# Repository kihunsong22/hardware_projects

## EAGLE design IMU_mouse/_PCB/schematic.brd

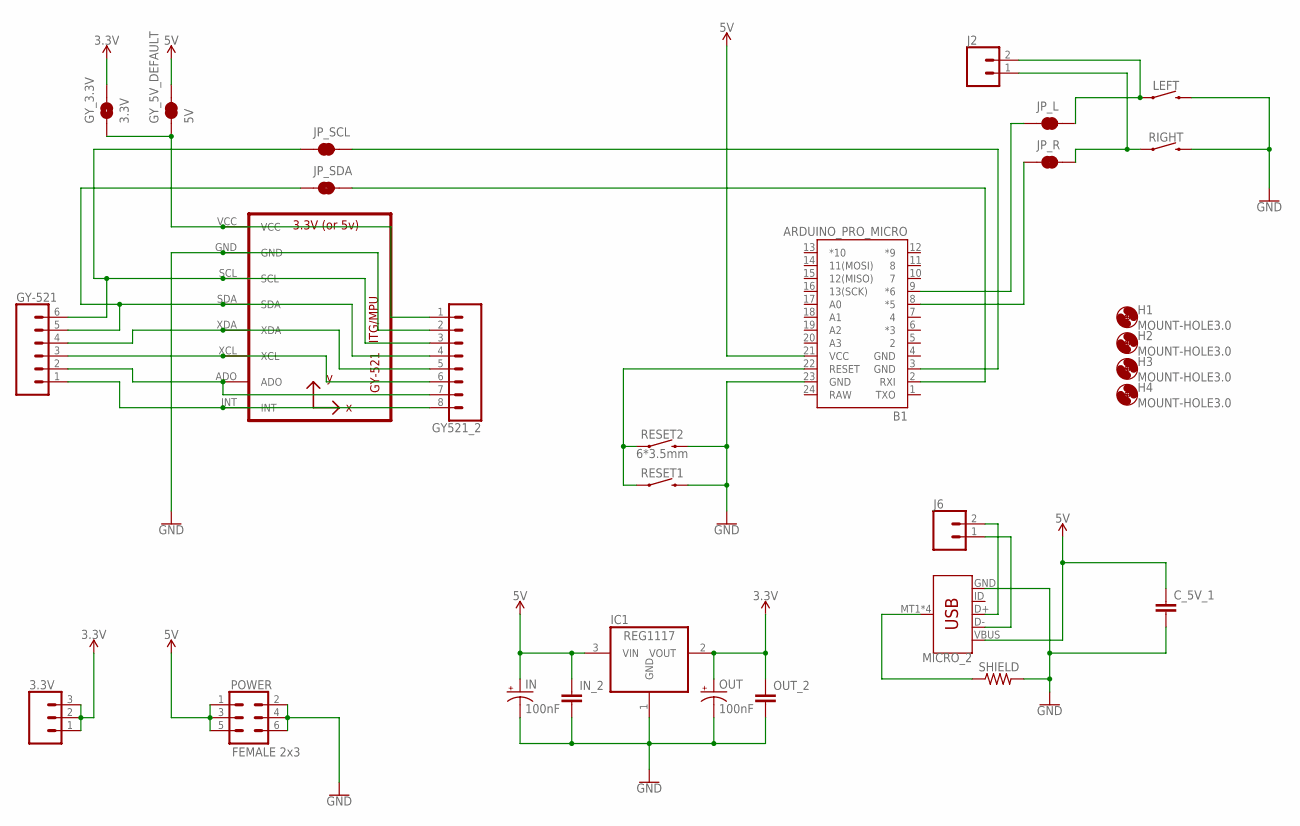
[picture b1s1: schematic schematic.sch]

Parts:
3.3V: CONN_03; 1X03
B1: ARDUINO_PRO_MICRO; SPARKFUN_PRO_MICRO
C_5V_1: C-EUC0805; C0805
GY521_2: CONN_08"; 1X08
GY-521: CONN_06LOCK; 1X06_LOCK
GY_3.3V: 3.3V; SMT-JUMPER_2_NO_NO-SILK
GY_5V_DEFAULT: 5V; SMT-JUMPER_2_NC_TRACE_SILK
H1, H2, H3, H4: MOUNT-HOLE3.0; 3,0
IC1: REG1117; SOT223
IN: 100nF; E2,5-5
IN_2: C-EUC0805; C0805
J2, J6: CONN_02LOCK; 1X02_LOCK
JP_L: JUMPER-SMT_2_NC_TRACE_SILK; SMT-JUMPER_2_NC_TRACE_SILK
JP_R: JUMPER-SMT_2_NC_TRACE_SILK; SMT-JUMPER_2_NC_TRACE_SILK
JP_SCL: JUMPER-SMT_2_NC_TRACE_SILK; SMT-JUMPER_2_NC_TRACE_SILK
JP_SDA: JUMPER-SMT_2_NC_TRACE_SILK; SMT-JUMPER_2_NC_TRACE_SILK
LEFT: MOMENTARY-SWITCH-SPST-PTH-6.0MM; TACTILE_SWITCH_PTH_6.0MM
MICRO_2: USB_MICRO-B_SMT; USB-MICROB
OUT: 100nF; E2,5-5
OUT_2: C-EUC0805; C0805
POWER: FEMALE 2x3; 2X3
RESET1: MOMENTARY-SWITCH-SPST-PTH-6.0MM; TACTILE_SWITCH_PTH_6.0MM
RESET2: 6*3.5mm; TACTILE_SWITCH_SMD_6.0X3.5MM
RIGHT: MOMENTARY-SWITCH-SPST-PTH-6.0MM; TACTILE_SWITCH_PTH_6.0MM
SHIELD: R-US_R0805; R0805
U1: GY-521MPU6050; GY-521

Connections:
3.3V: 3.3V.1, 3.3V.2, 3.3V.3, GY_3.3V.2, IC1.2 (VOUT), OUT.+, OUT_2.1
5V: B1.21 (VCC), C_5V_1.1, GY_5V_DEFAULT.2, IC1.3 (VIN), IN.+, IN_2.1, MICRO_2.VBUS, POWER.1, POWER.3, POWER.5
D+: J6.2, MICRO_2.D+
D-: J6.1, MICRO_2.D-
GND: B1.4 (GND), B1.23 (GND), C_5V_1.2, GY521_2.2, IC1.1 (GND), IN.-, IN_2.2, LEFT.3 (2), MICRO_2.GND, OUT.-, OUT_2.2, POWER.2, POWER.4, POWER.6, RESET1.3 (2), RESET2.2, RIGHT.3 (2), SHIELD.2, U1.GND
unnamed: J2.2, JP_L.2, LEFT.1
unnamed: J2.1, JP_R.2, RIGHT.1
unnamed: B1.8 (*5), JP_R.1
unnamed: B1.9 (*6), JP_L.1
unnamed: GY521_2.1, GY_3.3V.1, GY_5V_DEFAULT.1, U1.VCC
unnamed: B1.22 (RESET), RESET1.1, RESET2.1
unnamed: MICRO_2.MT1 (SHIELD), MICRO_2.MT2 (SHIELD), MICRO_2.P$1 (SHIELD), MICRO_2.P$2 (SHIELD), SHIELD.1
unnamed: B1.2 (RXI), JP_SDA.2
unnamed: B1.3 (GND), JP_SCL.2
unnamed: GY521_2.8, GY-521.1, U1.INT
unnamed: GY521_2.7, GY-521.2, U1.ADO
unnamed: GY521_2.6, GY-521.3, U1.XCL
unnamed: GY521_2.5, GY-521.4, U1.XDA
RAW: B1.24 (RAW)
SCL: GY521_2.3, GY-521.6, JP_SCL.1, U1.SCL
SDA: GY521_2.4, GY-521.5, JP_SDA.1, U1.SDA

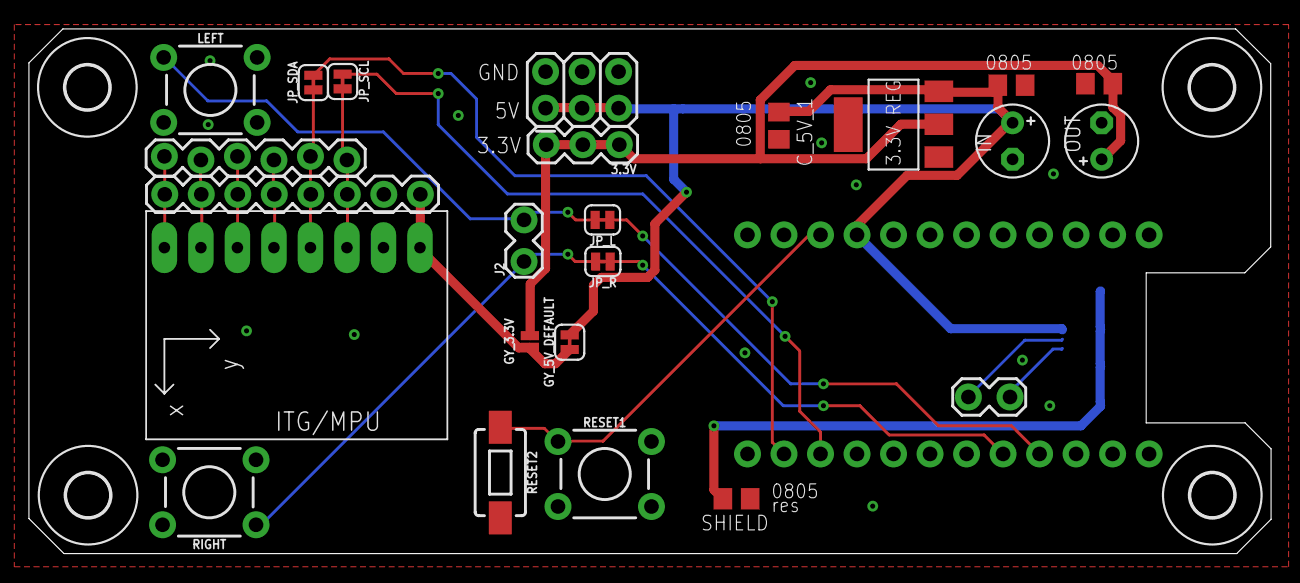
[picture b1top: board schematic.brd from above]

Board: 2 copper layers, 86.4 x 36.5 mm, 30 parts (1 on the bottom side), 20 nets.

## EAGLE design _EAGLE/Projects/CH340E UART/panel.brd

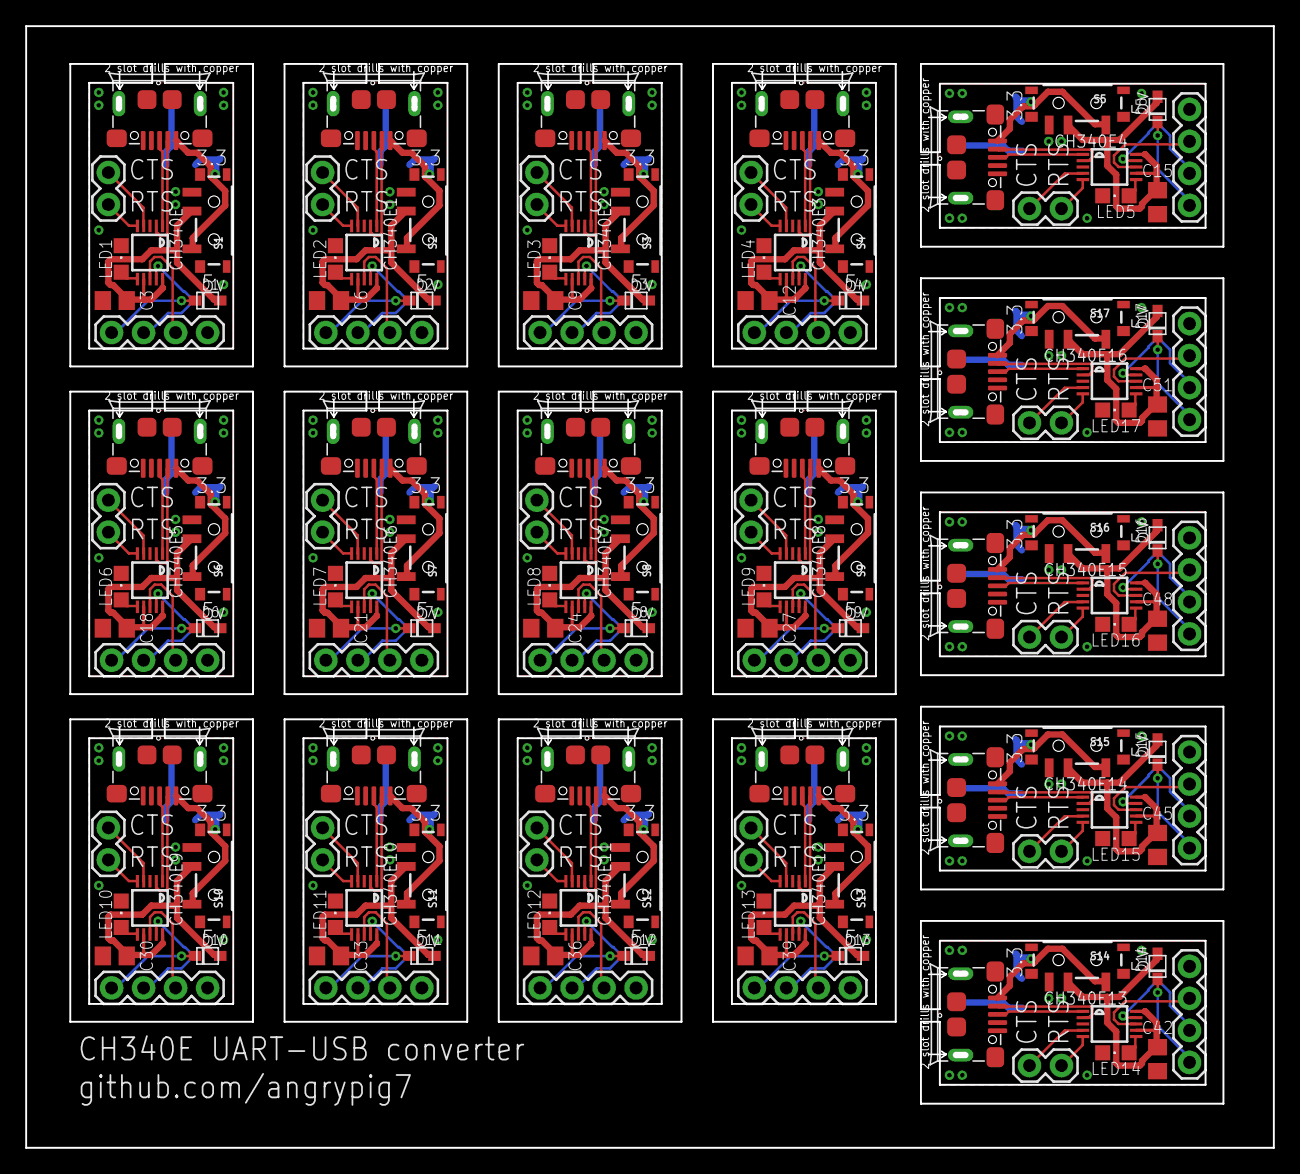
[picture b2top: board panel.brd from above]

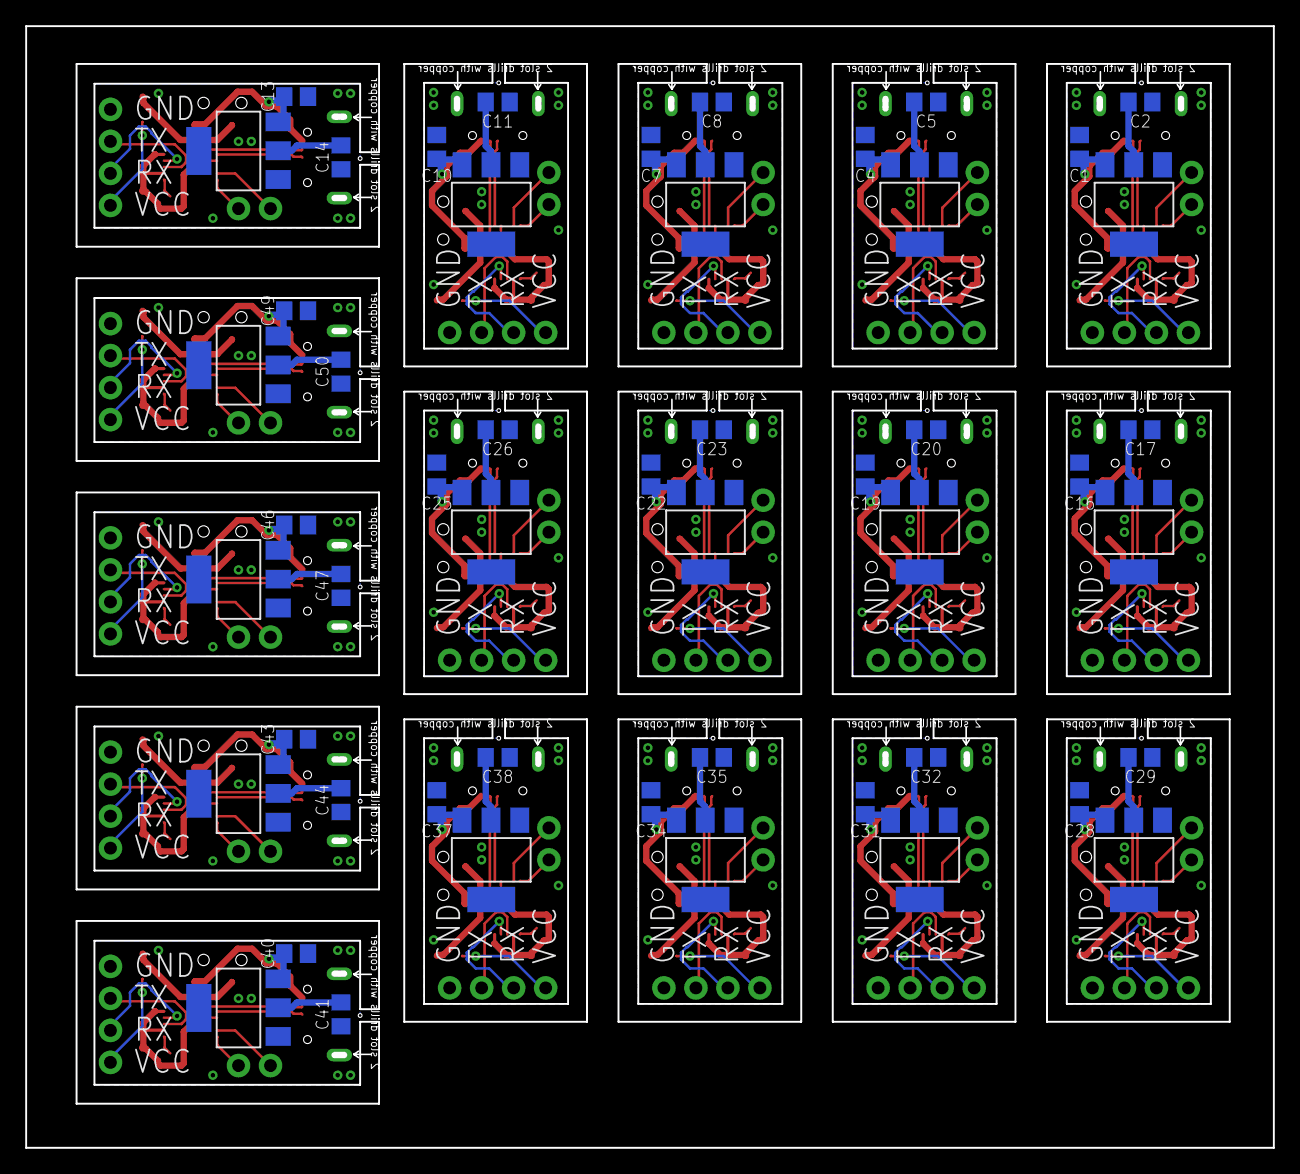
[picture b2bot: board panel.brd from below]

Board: 2 copper layers, 99.0 x 89.0 mm, 187 parts (51 on the bottom side), 204 nets.

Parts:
C1, C2, C3, C4, C5, C6, C7, C8, C9, C10, C11, C12, C13, C14, C15, C16, C17, C18, C19, C20, C21, C22, C23, C24, C25, C26, C27, C28, C29, C30, C31, C32, C33, C34, C35, C36, C37, C38, C39, C40, C41, C42, C43, C44, C45, C46, C47, C48, C49, C50, C51: 100nF; C0805
CH340E, CH340E1, CH340E2, CH340E3, CH340E4, CH340E5, CH340E6, CH340E7, CH340E8, CH340E9, CH340E10, CH340E11, CH340E12, CH340E13, CH340E14, CH340E15, CH340E16: CH340ESMD; MSOP10
D1, D2, D3, D4, D5, D6, D7, D8, D9, D10, D11, D12, D13, D14, D15, D16, D17: SOD-323F
IC1, IC2, IC3, IC4, IC5, IC6, IC7, IC8, IC9, IC10, IC11, IC12, IC13, IC14, IC15, IC16, IC17: REG1117; SOT223
J1, J3, J5, J7, J9, J11, J13, J15, J17, J19, J21, J23, J25, J27, J29, J31, J33: 1X04
J2, J4, J6, J8, J10, J12, J14, J16, J18, J20, J22, J24, J26, J28, J30, J32, J34: 1X02
LED1, LED2, LED3, LED4, LED5, LED6, LED7, LED8, LED9, LED10, LED11, LED12, LED13, LED14, LED15, LED16, LED17: CHIPLED_0805
S1, S2, S3, S4, S5, S6, S7, S8, S9, S10, S11, S12, S13, S14, S15, S16, S17: SWITCH_SPST_SMD_A
USB1, USB2, USB3, USB4, USB5, USB6, USB7, USB8, USB9, USB10, USB11, USB12, USB13, USB14, USB15, USB16, USB17: ST-USB-001G; MICRO-USB5+4P-SMD-0.65-B

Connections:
3V1: C5.1, IC2.2
3V2: C8.1, IC3.2
3V3: C2.1, IC1.2
3V4: C11.1, IC4.2
3V5: C14.1, IC5.2
3V6: C17.1, IC6.2
3V7: C20.1, IC7.2
3V8: C23.1, IC8.2
3V9: C26.1, IC9.2
3V10: C29.1, IC10.2
3V11: C32.1, IC11.2
3V12: C35.1, IC12.2
3V13: C38.1, IC13.2
3V14: C41.1, IC14.2
3V15: C44.1, IC15.2
3V16: C47.1, IC16.2
3V17: C50.1, IC17.2
5V: C1.1, IC1.3, S1.3, USB2.1
5V1: C4.1, IC2.3, S2.3, USB1.1
5V2: C7.1, IC3.3, S3.3, USB3.1
5V3: C10.1, IC4.3, S4.3, USB4.1
5V4: C13.1, IC5.3, S5.3, USB5.1
5V5: C16.1, IC6.3, S6.3, USB6.1
5V6: C19.1, IC7.3, S7.3, USB7.1
5V7: C22.1, IC8.3, S8.3, USB8.1
5V8: C25.1, IC9.3, S9.3, USB9.1
5V9: C28.1, IC10.3, S10.3, USB10.1
5V10: C31.1, IC11.3, S11.3, USB11.1
5V11: C34.1, IC12.3, S12.3, USB12.1
5V12: C37.1, IC13.3, S13.3, USB13.1
5V13: C40.1, IC14.3, S14.3, USB14.1
5V14: C43.1, IC15.3, S15.3, USB15.1
5V15: C46.1, IC16.3, S16.3, USB16.1
5V16: C49.1, IC17.3, S17.3, USB17.1
CTS: CH340E.5, J2.1
CTS1: CH340E1.5, J4.1
CTS2: CH340E2.5, J6.1
CTS3: CH340E3.5, J8.1
CTS4: CH340E4.5, J10.1
CTS5: CH340E5.5, J12.1
CTS6: CH340E6.5, J14.1
CTS7: CH340E7.5, J16.1
CTS8: CH340E8.5, J18.1
CTS9: CH340E9.5, J20.1
CTS10: CH340E10.5, J22.1
CTS11: CH340E11.5, J24.1
CTS12: CH340E12.5, J26.1
CTS13: CH340E13.5, J28.1
CTS14: CH340E14.5, J30.1
CTS15: CH340E15.5, J32.1
CTS16: CH340E16.5, J34.1
GND: C1.2, C2.2, C3.2, CH340E.3, IC1.1, J1.4, LED1.C, USB2.5, USB2.S1, USB2.S2, USB2.S3, USB2.S4, USB2.S5, USB2.S6
GND1: C4.2, C5.2, C6.2, CH340E1.3, IC2.1, J3.4, LED2.C, USB1.5, USB1.S1, USB1.S2, USB1.S3, USB1.S4, USB1.S5, USB1.S6
GND2: C7.2, C8.2, C9.2, CH340E2.3, IC3.1, J5.4, LED3.C, USB3.5, USB3.S1, USB3.S2, USB3.S3, USB3.S4, USB3.S5, USB3.S6
GND3: C10.2, C11.2, C12.2, CH340E3.3, IC4.1, J7.4, LED4.C, USB4.5, USB4.S1, USB4.S2, USB4.S3, USB4.S4, USB4.S5, USB4.S6
GND4: C13.2, C14.2, C15.2, CH340E4.3, IC5.1, J9.4, LED5.C, USB5.5, USB5.S1, USB5.S2, USB5.S3, USB5.S4, USB5.S5, USB5.S6
GND5: C16.2, C17.2, C18.2, CH340E5.3, IC6.1, J11.4, LED6.C, USB6.5, USB6.S1, USB6.S2, USB6.S3, USB6.S4, USB6.S5, USB6.S6
GND6: C19.2, C20.2, C21.2, CH340E6.3, IC7.1, J13.4, LED7.C, USB7.5, USB7.S1, USB7.S2, USB7.S3, USB7.S4, USB7.S5, USB7.S6
GND7: C22.2, C23.2, C24.2, CH340E7.3, IC8.1, J15.4, LED8.C, USB8.5, USB8.S1, USB8.S2, USB8.S3, USB8.S4, USB8.S5, USB8.S6
GND8: C25.2, C26.2, C27.2, CH340E8.3, IC9.1, J17.4, LED9.C, USB9.5, USB9.S1, USB9.S2, USB9.S3, USB9.S4, USB9.S5, USB9.S6
GND9: C28.2, C29.2, C30.2, CH340E9.3, IC10.1, J19.4, LED10.C, USB10.5, USB10.S1, USB10.S2, USB10.S3, USB10.S4, USB10.S5, USB10.S6
GND10: C31.2, C32.2, C33.2, CH340E10.3, IC11.1, J21.4, LED11.C, USB11.5, USB11.S1, USB11.S2, USB11.S3, USB11.S4, USB11.S5, USB11.S6
GND11: C34.2, C35.2, C36.2, CH340E11.3, IC12.1, J23.4, LED12.C, USB12.5, USB12.S1, USB12.S2, USB12.S3, USB12.S4, USB12.S5, USB12.S6
GND12: C37.2, C38.2, C39.2, CH340E12.3, IC13.1, J25.4, LED13.C, USB13.5, USB13.S1, USB13.S2, USB13.S3, USB13.S4, USB13.S5, USB13.S6
GND13: C40.2, C41.2, C42.2, CH340E13.3, IC14.1, J27.4, LED14.C, USB14.5, USB14.S1, USB14.S2, USB14.S3, USB14.S4, USB14.S5, USB14.S6
GND14: C43.2, C44.2, C45.2, CH340E14.3, IC15.1, J29.4, LED15.C, USB15.5, USB15.S1, USB15.S2, USB15.S3, USB15.S4, USB15.S5, USB15.S6
GND15: C46.2, C47.2, C48.2, CH340E15.3, IC16.1, J31.4, LED16.C, USB16.5, USB16.S1, USB16.S2, USB16.S3, USB16.S4, USB16.S5, USB16.S6
GND16: C49.2, C50.2, C51.2, CH340E16.3, IC17.1, J33.4, LED17.C, USB17.5, USB17.S1, USB17.S2, USB17.S3, USB17.S4, USB17.S5, USB17.S6
unnamed: CH340E.6, LED1.A
unnamed: CH340E1.6, LED2.A
unnamed: CH340E2.6, LED3.A
unnamed: CH340E3.6, LED4.A
unnamed: CH340E4.6, LED5.A
unnamed: CH340E5.6, LED6.A
unnamed: CH340E6.6, LED7.A
unnamed: CH340E7.6, LED8.A
unnamed: CH340E8.6, LED9.A
unnamed: CH340E9.6, LED10.A
unnamed: CH340E10.6, LED11.A
unnamed: CH340E11.6, LED12.A
unnamed: CH340E12.6, LED13.A
unnamed: CH340E13.6, LED14.A
unnamed: CH340E14.6, LED15.A
unnamed: CH340E15.6, LED16.A
unnamed: CH340E16.6, LED17.A
RTS: CH340E.4, J2.2
RTS1: CH340E1.4, J4.2
RTS2: CH340E2.4, J6.2
RTS3: CH340E3.4, J8.2
RTS4: CH340E4.4, J10.2
RTS5: CH340E5.4, J12.2
RTS6: CH340E6.4, J14.2
RTS7: CH340E7.4, J16.2
RTS8: CH340E8.4, J18.2
RTS9: CH340E9.4, J20.2
RTS10: CH340E10.4, J22.2
RTS11: CH340E11.4, J24.2
RTS12: CH340E12.4, J26.2
RTS13: CH340E13.4, J28.2
RTS14: CH340E14.4, J30.2
RTS15: CH340E15.4, J32.2
RTS16: CH340E16.4, J34.2
RX: CH340E.9, J1.2
RX1: CH340E1.9, J3.2
RX2: CH340E2.9, J5.2
RX3: CH340E3.9, J7.2
RX4: CH340E4.9, J9.2
RX5: CH340E5.9, J11.2
RX6: CH340E6.9, J13.2
RX7: CH340E7.9, J15.2
RX8: CH340E8.9, J17.2
RX9: CH340E9.9, J19.2
RX10: CH340E10.9, J21.2
RX11: CH340E11.9, J23.2
RX12: CH340E12.9, J25.2
RX13: CH340E13.9, J27.2
RX14: CH340E14.9, J29.2
RX15: CH340E15.9, J31.2
RX16: CH340E16.9, J33.2
TX: CH340E.8, J1.3
TX1: CH340E1.8, J3.3
TX2: CH340E2.8, J5.3
TX3: CH340E3.8, J7.3
TX4: CH340E4.8, J9.3
TX5: CH340E5.8, J11.3
TX6: CH340E6.8, J13.3
TX7: CH340E7.8, J15.3
TX8: CH340E8.8, J17.3
TX9: CH340E9.8, J19.3
TX10: CH340E10.8, J21.3
TX11: CH340E11.8, J23.3
TX12: CH340E12.8, J25.3
TX13: CH340E13.8, J27.3
TX14: CH340E14.8, J29.3
TX15: CH340E15.8, J31.3
TX16: CH340E16.8, J33.3
USBN: CH340E.2, USB2.2
USBN1: CH340E1.2, USB1.2
USBN2: CH340E2.2, USB3.2
USBN3: CH340E3.2, USB4.2
USBN4: CH340E4.2, USB5.2
USBN5: CH340E5.2, USB6.2
USBN6: CH340E6.2, USB7.2
USBN7: CH340E7.2, USB8.2
USBN8: CH340E8.2, USB9.2
USBN9: CH340E9.2, USB10.2
USBN10: CH340E10.2, USB11.2
USBN11: CH340E11.2, USB12.2
USBN12: CH340E12.2, USB13.2
USBN13: CH340E13.2, USB14.2
USBN14: CH340E14.2, USB15.2
USBN15: CH340E15.2, USB16.2
USBN16: CH340E16.2, USB17.2
USBP: CH340E.1, USB2.3
USBP1: CH340E1.1, USB1.3
USBP2: CH340E2.1, USB3.3
USBP3: CH340E3.1, USB4.3
USBP4: CH340E4.1, USB5.3
USBP5: CH340E5.1, USB6.3
USBP6: CH340E6.1, USB7.3
USBP7: CH340E7.1, USB8.3
USBP8: CH340E8.1, USB9.3
USBP9: CH340E9.1, USB10.3
USBP10: CH340E10.1, USB11.3
USBP11: CH340E11.1, USB12.3
USBP12: CH340E12.1, USB13.3
USBP13: CH340E13.1, USB14.3
USBP14: CH340E14.1, USB15.3
USBP15: CH340E15.1, USB16.3
USBP16: CH340E16.1, USB17.3
VCC: C3.1, CH340E.7, CH340E.10, D1.A, S1.2
VCC1: C6.1, CH340E1.7, CH340E1.10, D2.A, S2.2
VCC2: C9.1, CH340E2.7, CH340E2.10, D3.A, S3.2
VCC3: C12.1, CH340E3.7, CH340E3.10, D4.A, S4.2
VCC4: C15.1, CH340E4.7, CH340E4.10, D5.A, S5.2
VCC5: C18.1, CH340E5.7, CH340E5.10, D6.A, S6.2
VCC6: C21.1, CH340E6.7, CH340E6.10, D7.A, S7.2
VCC7: C24.1, CH340E7.7, CH340E7.10, D8.A, S8.2
VCC8: C27.1, CH340E8.7, CH340E8.10, D9.A, S9.2
VCC9: C30.1, CH340E9.7, CH340E9.10, D10.A, S10.2
VCC10: C33.1, CH340E10.7, CH340E10.10, D11.A, S11.2
VCC11: C36.1, CH340E11.7, CH340E11.10, D12.A, S12.2
VCC12: C39.1, CH340E12.7, CH340E12.10, D13.A, S13.2
VCC13: C42.1, CH340E13.7, CH340E13.10, D14.A, S14.2
VCC14: C45.1, CH340E14.7, CH340E14.10, D15.A, S15.2
VCC15: C48.1, CH340E15.7, CH340E15.10, D16.A, S16.2
VCC16: C51.1, CH340E16.7, CH340E16.10, D17.A, S17.2
VCC_D: D1.C, J1.1
VCC_D1: D2.C, J3.1
VCC_D2: D3.C, J5.1
VCC_D3: D4.C, J7.1
VCC_D4: D5.C, J9.1
VCC_D5: D6.C, J11.1
VCC_D6: D7.C, J13.1
VCC_D7: D8.C, J15.1
VCC_D8: D9.C, J17.1
VCC_D9: D10.C, J19.1
VCC_D10: D11.C, J21.1
VCC_D11: D12.C, J23.1
VCC_D12: D13.C, J25.1
VCC_D13: D14.C, J27.1
VCC_D14: D15.C, J29.1
VCC_D15: D16.C, J31.1
VCC_D16: D17.C, J33.1

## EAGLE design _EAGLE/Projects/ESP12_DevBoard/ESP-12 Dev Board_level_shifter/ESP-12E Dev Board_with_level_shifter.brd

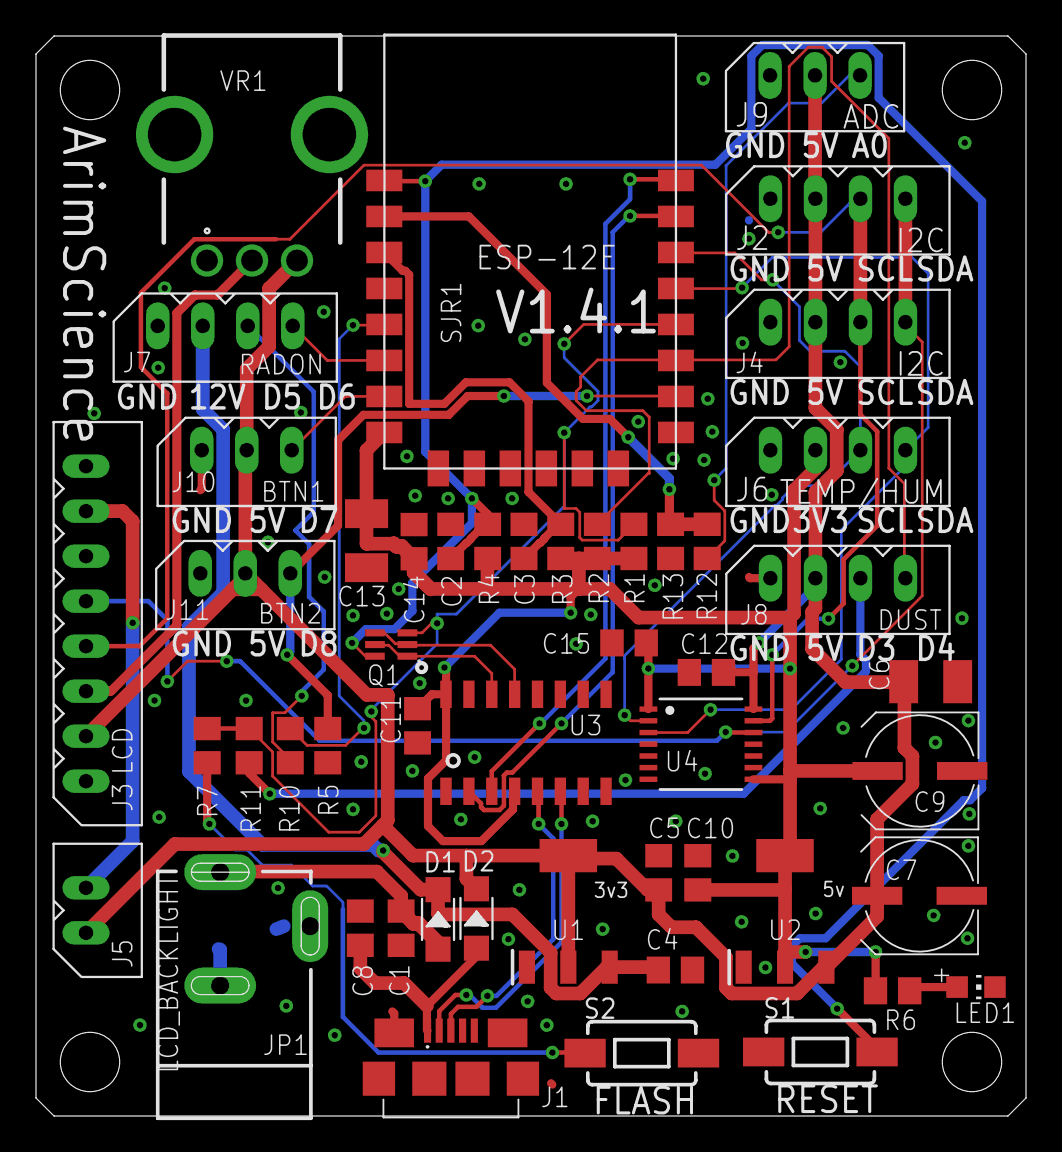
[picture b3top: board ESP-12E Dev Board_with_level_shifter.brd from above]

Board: 2 copper layers, 55.0 x 60.0 mm, 50 parts (0 on the bottom side), 32 nets.

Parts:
C1, C4: 10uF; C0805
C2, C3, C8, C11, C12, C14, C15: 100nF; C0805
C5, C10: 22uF; C0805
C6, C13: 100uF; SMC_B
C7, C9: 220uF; UD-6,3X7,7_NICHICON
D1, D2: 1N5819W; SOD-123
J1: ZX62-B-5PA(33); ZX62B5PA33
J2, J4: I2C; 5267-4
J3: LCD; 5267-8
J5: LCD_BACKLIGHT; 5267-2
J6: TEMP/HUM; 5267-4
J7: RADON; 5267-4
J8: DUST; 5267-4
J9: ADC; 5267-3
J10: BTN1; 5267-3
J11: BTN2; 5267-3
JP1: POWER_JACKSLT; POWER_JACK_SLOT
LED1: green; CHIP-LED0805
Q1: UMH3N; SOT65P210X100-6N
R1, R2, R3, R4, R5, R6: 10k; R0805
R7, R10, R11: 470Ω; R0805
R12: 47k(1%); R0805
R13: 10k(1%); R0805
S1: RST; TACTILE_SWITCH_SMD_6.0X3.5MM
S2: FLASH; TACTILE_SWITCH_SMD_6.0X3.5MM
SJR1: ESP-12E; ESP8266-ESP12E
U1: 5V_REG; SOT230P700X170-4N
U2: 3V3_REG; SOT230P700X170-4N
U3: CH340C; SOIC16
U4: TXS0104; TSSOP14
VR1: RK09K1130AAU; RK09K1130BGM

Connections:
3.3V: C9.+, C10.2, C11.2, C13.+, C14.2, C15.2, J6.P$2, R1.1, R2.1, R3.1, R4.1, R6.1, SJR1.8, U2.2, U2.4, U3.4, U3.16, U4.1, U4.8
5V: C5.1, C6.+, C7.+, C12.2, D2.-, J2.P$2, J3.P$2, J4.P$2, J5.P$1, J8.P$2, J9.P$2, J10.P$2, J11.P$2, U1.2, U1.4, U2.3, U4.14, VR1.3
12V: C4.1, D1.-, J7.P$2, U1.3
ADC: R12.1, R13.2, SJR1.2
D+_USB: J1.D+, U3.5
D-_USB: J1.D-, U3.6
DTR: Q1.2, Q1.4, U3.13
EN: C3.2, R3.2, SJR1.3
GND: C1.1, C2.1, C3.1, C4.2, C5.2, C6.-, C7.-, C8.1, C9.-, C10.1, C11.1, C12.1, C13.-, C14.1, C15.1, J1.GND, J1.SHIELD_1, J1.SHIELD_2, J1.SHIELD_3, J1.SHIELD_4, J1.SHIELD_5, J1.SHIELD_6, J2.P$1, J3.P$1, J3.P$8, J4.P$1, J6.P$1, J7.P$1, J8.P$1, J9.P$1, J10.P$1, J11.P$1, JP1.GND@1, JP1.GND@2, LED1.C, R5.1, R13.1, S1.2, S2.2, SJR1.9, U1.1, U2.1, U3.1, U4.7, VR1.1
GPIO0: Q1.3, R1.2, R7.1, R11.1, SJR1.12
GPIO2: J8.P$4, R2.2, SJR1.11
GPIO4: J6.P$4, SJR1.13, U4.3
GPIO5: J6.P$3, SJR1.14, U4.2
GPIO12: J7.P$4, SJR1.6
GPIO13: J10.P$3, SJR1.7
GPIO14: R10.1, SJR1.5
GPIO15: J11.P$3, R5.2, SJR1.10
LED+: J3.P$7, J5.P$2
unnamed: J3.P$3, VR1.2
unnamed: C1.2, D1.+, JP1.PWR
unnamed: LED1.A, R6.2
unnamed: J9.P$3, R12.2
unnamed: J7.P$3, R10.2
unnamed: J8.P$3, R11.2
unnamed: C8.2, D2.+, J1.VCC
POWER1: R7.2, S2.1
RST: C2.2, Q1.6, R4.2, S1.1, SJR1.1
RTS: Q1.1, Q1.5, U3.14
RXD: SJR1.15, U3.2
SCL_5V: J2.P$3, J3.P$4, J4.P$3, U4.13
SDA_5V: J2.P$4, J3.P$5, J4.P$4, U4.12
TXD: SJR1.16, U3.3

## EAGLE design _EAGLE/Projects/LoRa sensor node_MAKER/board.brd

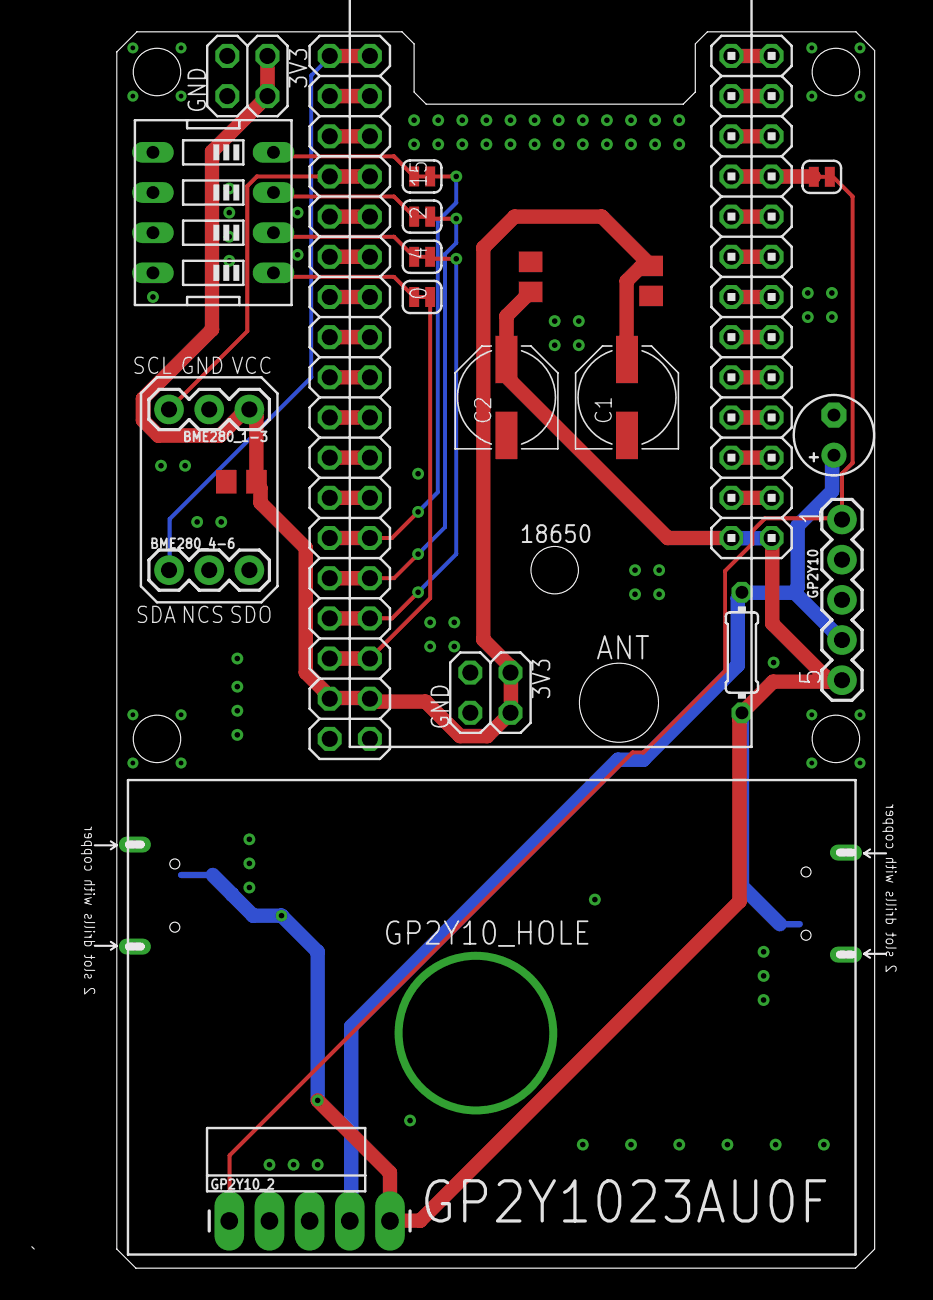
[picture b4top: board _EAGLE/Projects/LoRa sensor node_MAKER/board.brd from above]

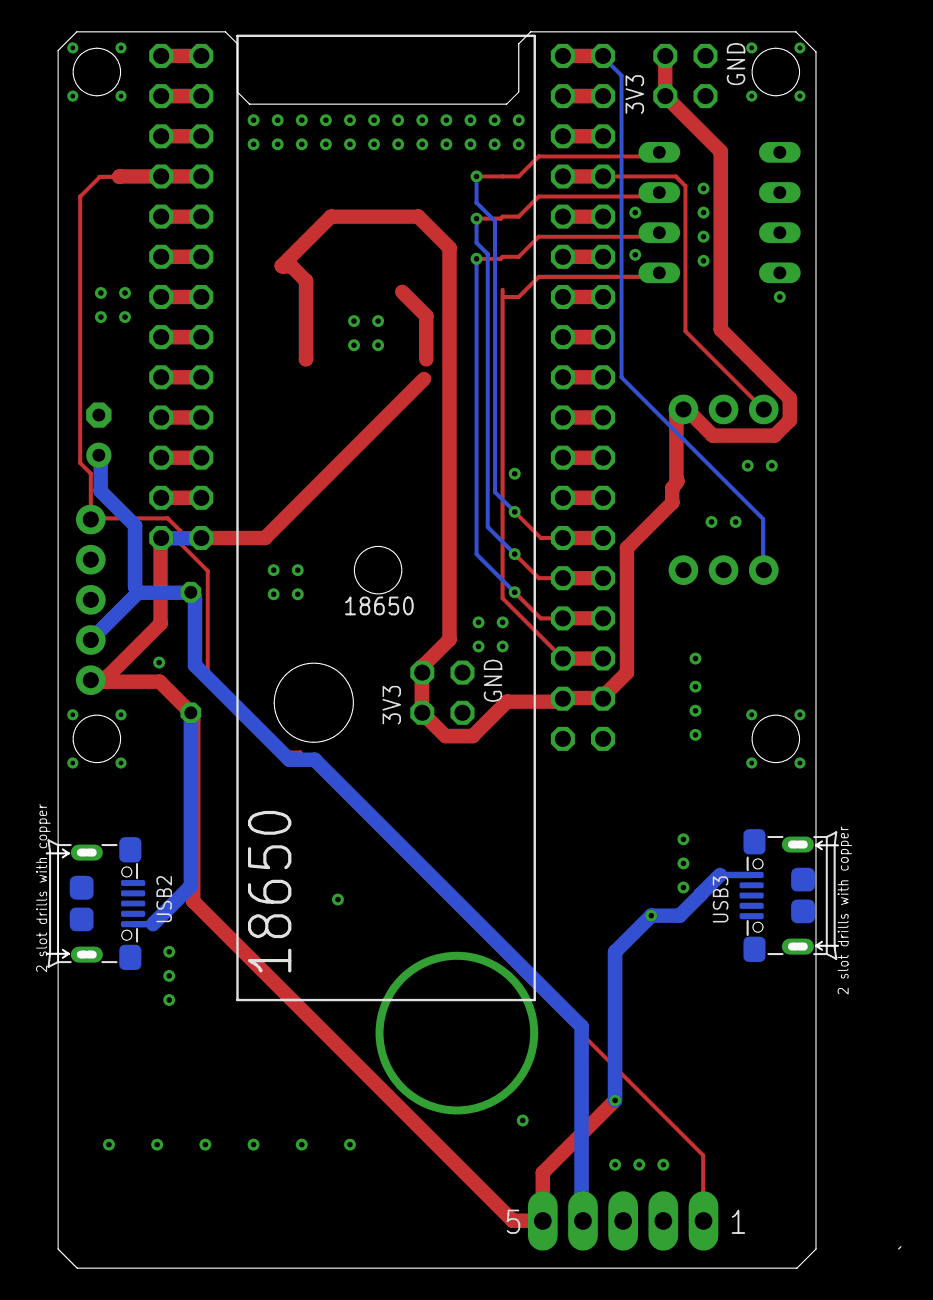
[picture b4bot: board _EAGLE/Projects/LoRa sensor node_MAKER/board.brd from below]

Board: 2 copper layers, 47.9 x 78.2 mm, 24 parts (2 on the bottom side), 36 nets.

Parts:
BME280_1-3, BME280_4-6: 1X03
C1, C2: PANASONIC_D
C3, C8, C9: 100nF; C0805
C6: 220uF; E2,5-5
GP2Y10: 1X05
GP2Y10_2: 1X05_LONGPADS
H1: DRILL_0.3650_GP2Y10; PAD_0.3650
JP1: Vout; SMT-JUMPER_2_NC_TRACE_SILK
JP2: 2X18
JP3: 2X13
JP4, JP5, JP6, JP7: SMT-JUMPER_2_NC_TRACE_SILK
JP8, JP9: 2X02
R1: 150Ω; 0204/7
SW1: EDG-04
USB2, USB3: ST-USB-001G; MICRO-USB5+4P-SMD-0.65-B

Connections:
3.3V: BME280_1-3.1, C1.+, C8.1, C9.2, JP2.3, JP2.4, JP8.1, JP8.2, JP9.1, JP9.2
5V: C2.+, C3.1, GP2Y10.5, GP2Y10_2.5, JP3.1, JP3.2, R1.2, USB2.5, USB3.5
DIP1: JP2.5, JP2.6, JP7.2
DIP2: JP2.7, JP2.8, JP6.2
DIP3: JP2.9, JP2.10, JP5.2
DIP4: JP2.11, JP2.12, JP4.2
GND: BME280_1-3.2, C1.-, C2.-, C3.2, C6.-, C8.2, C9.1, GP2Y10.2, GP2Y10.3, GP2Y10_2.2, GP2Y10_2.3, JP2.1, JP2.2, JP3.3, JP3.4, JP8.3, JP8.4, JP9.3, JP9.4, SW1.5, SW1.6, SW1.7, SW1.8, USB2.1, USB2.S1, USB2.S2, USB2.S3, USB2.S4, USB2.S5, USB2.S6, USB3.1, USB3.S1, USB3.S2, USB3.S3, USB3.S4, USB3.S5, USB3.S6
unnamed: JP7.1, SW1.1
unnamed: JP6.1, SW1.2
unnamed: JP2.33, JP2.34
unnamed: JP2.31, JP2.32
unnamed: JP2.27, JP2.28
unnamed: JP2.25, JP2.26
unnamed: JP3.25, JP3.26
unnamed: JP3.23, JP3.24
unnamed: JP3.21, JP3.22
unnamed: JP3.17, JP3.18
unnamed: JP5.1, SW1.3
unnamed: JP3.15, JP3.16
unnamed: JP3.13, JP3.14
unnamed: JP3.11, JP3.12
unnamed: JP3.9, JP3.10
unnamed: JP3.7, JP3.8
unnamed: JP3.5, JP3.6
unnamed: JP4.1, SW1.4
unnamed: JP2.13, JP2.14
unnamed: JP2.15, JP2.16
unnamed: JP2.17, JP2.18
unnamed: JP2.19, JP2.20
unnamed: JP2.21, JP2.22
unnamed: JP2.23, JP2.24
SCL: BME280_1-3.3, JP2.29, JP2.30
SDA: BME280_4-6.1, JP2.35, JP2.36
VLED: C6.+, GP2Y10.4, GP2Y10_2.4, R1.1
VOUT: JP1.2, JP3.19, JP3.20
VOUT_1: GP2Y10.1, GP2Y10_2.1, JP1.1

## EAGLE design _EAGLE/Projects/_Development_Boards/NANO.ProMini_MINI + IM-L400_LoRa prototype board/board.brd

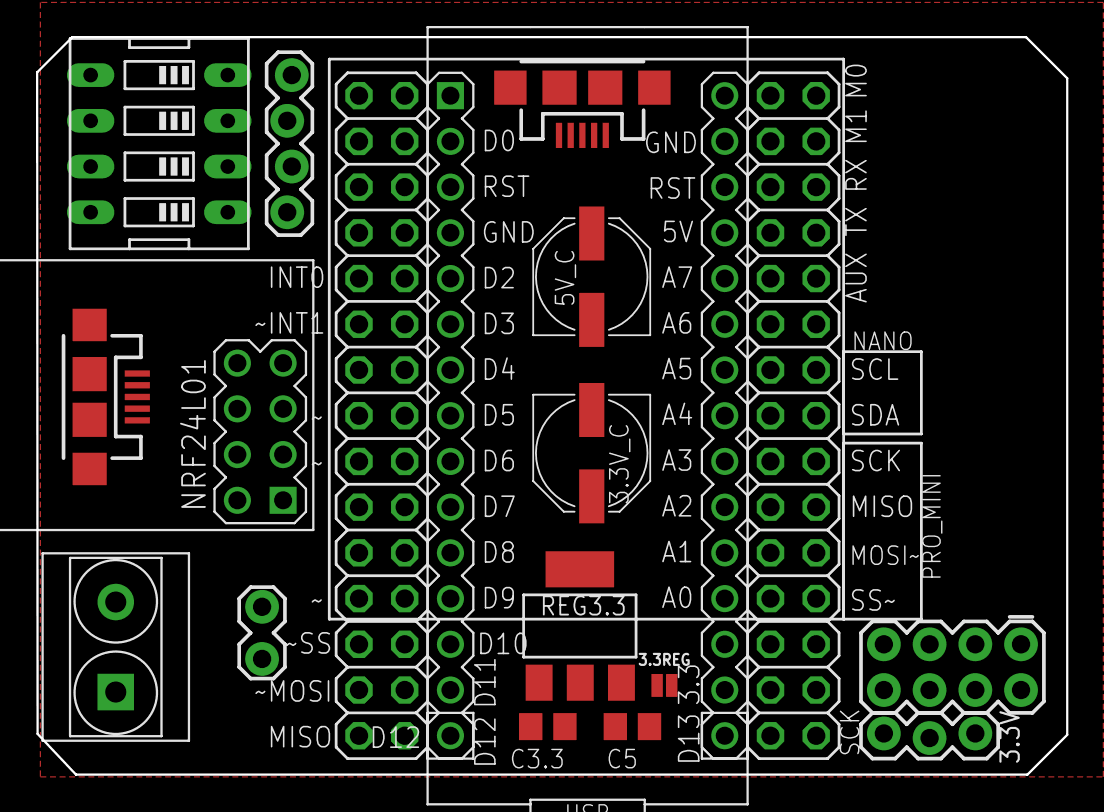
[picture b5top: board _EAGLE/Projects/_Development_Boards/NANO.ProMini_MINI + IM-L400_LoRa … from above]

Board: 2 copper layers, 57.2 x 41.0 mm, 18 parts (0 on the bottom side), 38 nets, no tracks yet.

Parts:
3.3REG: SMT-JUMPER_2_NO_NO-SILK
3.3V: 1X03_LOCK
3.3V_C, 5V_C: PANASONIC_D
5.GND: 2X4
C3.3, C5: 100nF; C0805
J4: 1X04_LOCK
MICRO_1, MICRO_2: USB-MICROB
NANO: ARDUINO-NANO-3.0
NRF24L01: WIRELESS-NRF24L01
PH1, PH2: 2X15
PIN1: 1X02_LOCK
REG3.3: REG1117; SOT223
SW1: EDG-04
T1_5MM: 5mm; H2-5.0-10.5X8.0MM

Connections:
3.3V: 3.3V.1, 3.3V.2, 3.3V.3, 3.3V_C.+, NANO.J2.14, NRF24L01.2, PH1.3, PH1.4
5V: 5.GND.2, 5.GND.4, 5.GND.6, 5.GND.8, 5V_C.+, C5.1, MICRO_1.VBUS, MICRO_2.VBUS, NANO.J2.4, PH1.23, PH1.24, REG3.3.3
A5: NANO.J2.7, PH1.17, PH1.18
A6: NANO.J2.6, PH1.19, PH1.20
A7: NANO.J2.5, PH1.21, PH1.22
CE_NRF: NANO.J1.9, NRF24L01.3, PH2.13, PH2.14
CSN_NRF: NANO.J1.8, NRF24L01.4, PH2.15, PH2.16
GND: 3.3V_C.-, 5.GND.1, 5.GND.3, 5.GND.5, 5.GND.7, 5V_C.-, C3.3.1, C5.2, MICRO_1.GND, MICRO_2.GND, NANO.J2.2, NRF24L01.1, PH1.27, PH1.28, REG3.3.1, SW1.5, SW1.6, SW1.7, SW1.8
MISO_NRF: NANO.J1.4, NRF24L01.7, PH2.23, PH2.24
MOSI_NRF: NANO.J1.5, NRF24L01.6, PH2.21, PH2.22
unnamed: 3.3REG.2, C3.3.2
unnamed: 3.3REG.1, REG3.3.2
unnamed: NANO.J2.13, PH1.5, PH1.6
unnamed: NANO.J2.12, PH1.7, PH1.8
unnamed: NANO.J2.11, PH1.9, PH1.10
unnamed: NANO.J2.10, PH1.11, PH1.12
unnamed: NANO.J2.9, PH1.13, PH1.14
unnamed: NANO.J2.8, PH1.15, PH1.16
unnamed: NANO.J1.15, PH2.1, PH2.2
unnamed: NANO.J1.14, PH2.3, PH2.4
unnamed: NANO.J1.13, PH2.5, PH2.6
unnamed: NANO.J1.12, PH2.7, PH2.8
unnamed: NANO.J1.11, PH2.9, PH2.10
unnamed: NANO.J1.10, PH2.11, PH2.12
unnamed: PIN1.2, T1_5MM.1
unnamed: NANO.J1.7, PH2.17, PH2.18
unnamed: NANO.J1.6, PH2.19, PH2.20
unnamed: PIN1.1, T1_5MM.2
unnamed: NANO.J1.3, PH2.25, PH2.26
unnamed: NANO.J1.2, PH2.27, PH2.28
unnamed: NANO.J1.1, PH2.29, PH2.30
unnamed: J4.1, SW1.4
unnamed: J4.2, SW1.3
unnamed: J4.3, SW1.2
unnamed: J4.4, SW1.1
RST: NANO.J2.3, PH1.25, PH1.26
SCK_NRF: NANO.J2.15, NRF24L01.5, PH1.1, PH1.2
VIN: NANO.J2.1, PH1.29, PH1.30

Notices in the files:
parts and their libraries:
SparkFun-Connectors: Licensing: Creative Commons ShareAlike 4.0 International - https://creativecommons.org/licenses/by-sa/4.0
diy-modules: Released under the Creative Commons Attribution 4.0 International License: http://creativecommons.org/licenses/by/4.0
